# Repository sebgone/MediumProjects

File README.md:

# Electronics projects view

Medium size embedded electronics projects performed during studies.

1. [Bicycle Electronic Shifter](https://github.com/sebgone/MediumProjects/tree/main/Bicycle%20Electric%20Shifter)
2. [Blinds Control System](https://github.com/sebgone/MediumProjects/tree/main/Blinds%20Control%20System)
3. [Machine Learning Position Tracker](https://github.com/sebgone/MediumProjects/tree/main/Mchnie%20Learning%20Position%20Tracker)

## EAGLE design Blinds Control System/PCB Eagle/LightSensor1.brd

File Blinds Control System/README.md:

# Blinds Control System

The purpose of this project was designing and building a control system for monitoring and setting the amount of sunlight in the room. The major assumption was based on making use of wireless solutions to communicate between elements of control system. Its parts consist of regulator, driver element and sensors. The functioning comes to read data from light sensors compare this value with desired value and then applies the difference as a control signal to steer a roller blinds by DC motor. 

## Technology:
* Arduino 
* Ethernet Shield
* Bluetooth

## Application:
The system consist of four elements. Central Module is a master device which supervise data comunication beetwen DC controler and bluetooth sensors. 
User has accesss by a web browser to set a specific light level or read actual value. Sensors send readings to master and it calculte average. 
The calculated value is compared with desired value. Next, based on difference range DC controler get up or down blinds.    

## specificaton:
- Four elements of a system
- Bluetooth communication
- Sensor battery supply
- Controlling web page
- Limit switches 
- DC motor with metal gear
---
## Design:
* ### Source Code:
  * [source code](https://github.com/sebgone/MediumProjects/tree/sebgone-update/Blinds%20Control%20System/Source%20Code)  

* ### Block Scheme:

* ### Circuit Diagram:
&nbsp;
&nbsp;

  * Central module

&nbsp;
&nbsp;

  * Driver

&nbsp;
&nbsp;

  * Light Sensor

* ### Circuit Eagle schematic:
&nbsp;
&nbsp;

   * Light Sensor 

&nbsp;
&nbsp;

   * Motor Driver 

* ### Circuit Eagle PCB layout:
&nbsp;
&nbsp;

  * Light Sensor

&nbsp;
&nbsp;

  * Moto Driver

* ### Web Page:

* ### Assembled device:

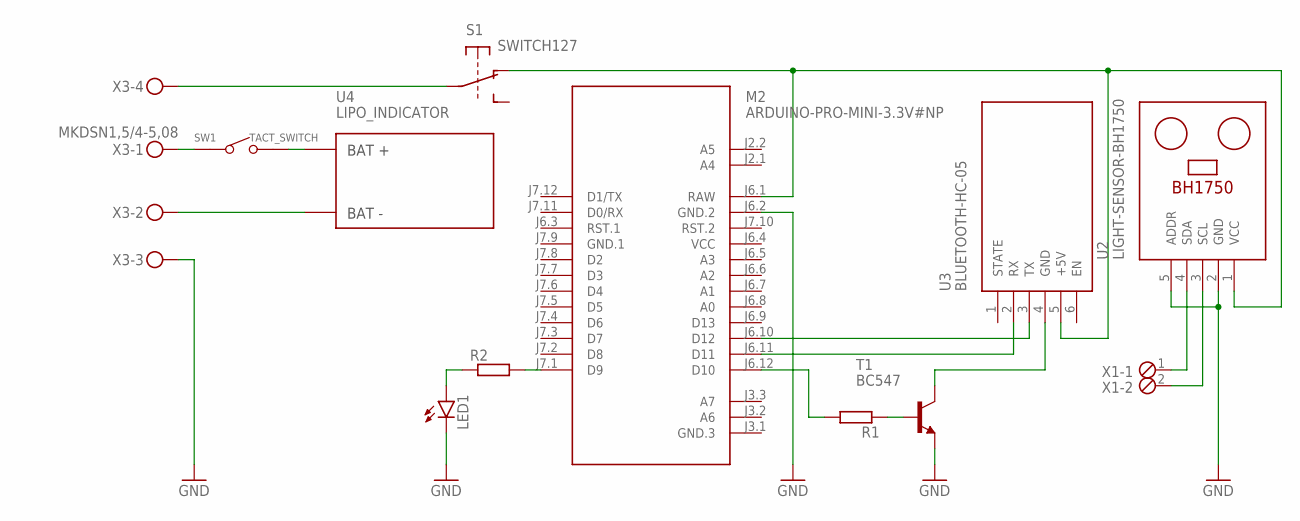
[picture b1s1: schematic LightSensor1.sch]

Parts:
LED1: LED3MM
M2: ARDUINO-PRO-MINI-3.3V#NP; ARDUINO-PRO-MINI#NP
R1, R2: R-EU_0207/10; 0207/10
S1: SWITCH127
SW1: TACT_SWITCH; SW2-5.0-6.0X3.0X4.3MM
T1: BC547; TO92
U2: LIGHT-SENSOR-BH1750
U3: BLUETOOTH-HC-05; WIRELESS-BLUETOOTH-HC-05
U4: LIPO_INDICATOR; INDICATROR_NR1
X1: MPT2; 2POL254
X3: MKDSN1,5/4-5,08

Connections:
GND: LED1.K (C), M2.J6.2 (GND.2), T1.1 (E), U2.2 (GND), U2.5 (ADDR), X3.3
GND.1: M2.J7.9 (GND.1)
unnamed: U4.-BAT, X3.2
unnamed: SW1.2, U4.+BAT
unnamed: SW1.1, X3.1
unnamed: M2.J6.11 (D11), U3.2 (RX)
unnamed: S1.P$2 (2), X3.4
unnamed: LED1.A, R2.1
unnamed: M2.J6.1 (RAW), S1.P$3 (3), U2.1 (VCC), U3.5 (+5V)
unnamed: M2.J7.1 (D9), R2.2
unnamed: M2.J6.10 (D12), U3.3 (TX)
unnamed: M2.J6.12 (D10), R1.2
unnamed: R1.1, T1.2 (B)
unnamed: T1.3 (C), U3.4 (GND)
unnamed: U2.4 (SDA), X1.1
unnamed: U2.3 (SCL), X1.2
VCC: M2.J6.4 (VCC)

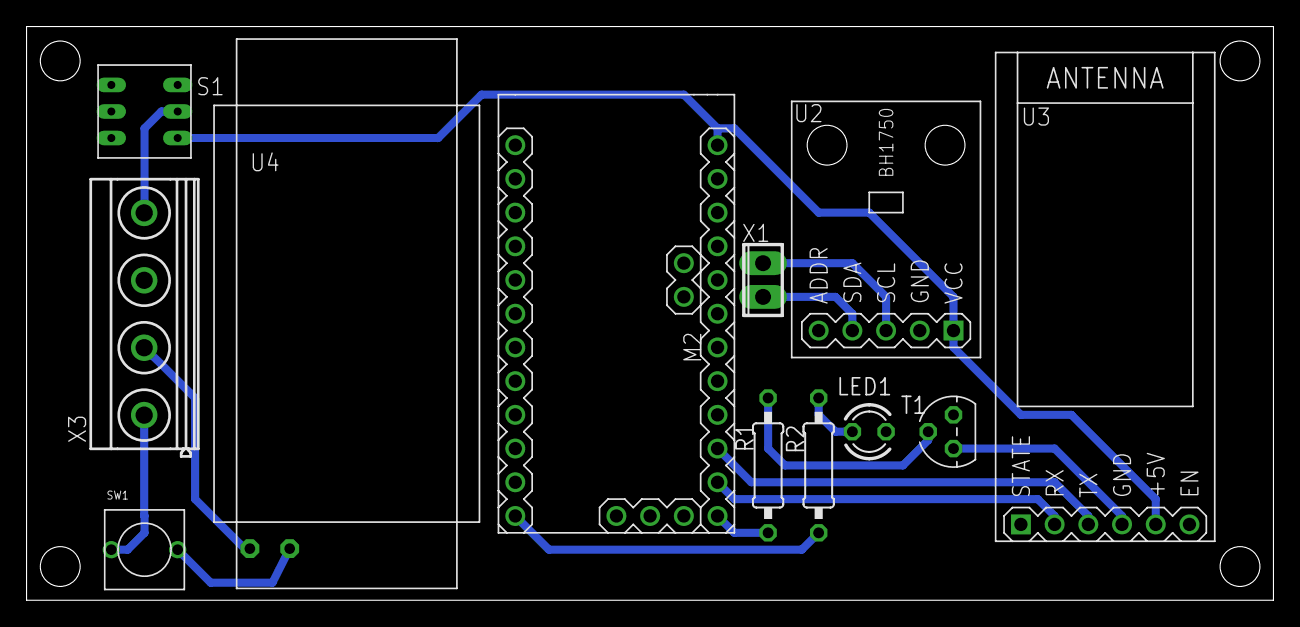
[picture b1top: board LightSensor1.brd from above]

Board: 2 copper layers, 94.0 x 43.2 mm, 12 parts (0 on the bottom side), 15 nets.

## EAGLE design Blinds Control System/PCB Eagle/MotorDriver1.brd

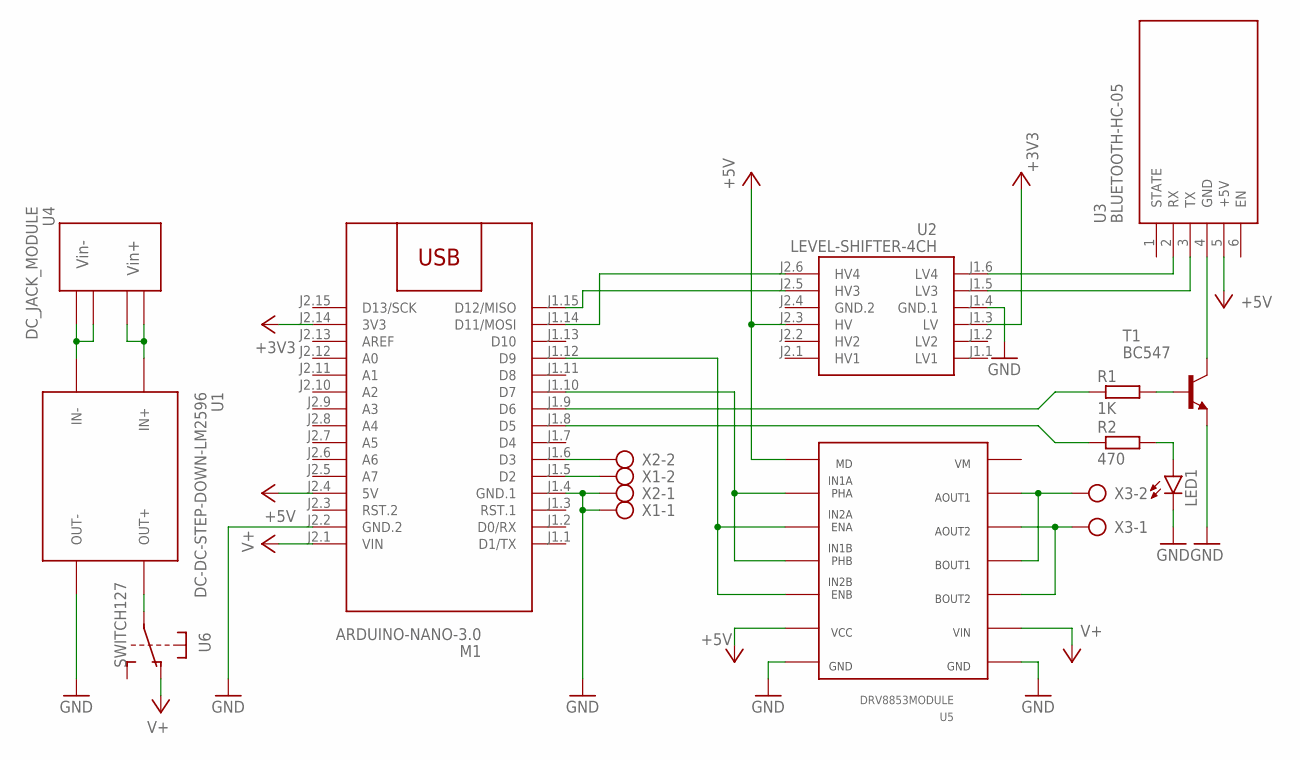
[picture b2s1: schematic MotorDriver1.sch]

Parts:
LED1: LED3MM
M1: ARDUINO-NANO-3.0
R1: 1K; 0207/7
R2: 470; 0207/7
T1: BC547; TO92
U1: DC-DC-STEP-DOWN-LM2596
U2: LEVEL-SHIFTER-4CH
U3: BLUETOOTH-HC-05; WIRELESS-BLUETOOTH-HC-05
U4: DC_JACK_MODULE; MA04-1
U5: DRV8853MODULE; DIL14
U6: SWITCH127
X1, X2, X3: AK500/2

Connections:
+3V3: M1.J2.14 (3V3), U2.J1.3 (LV)
+5V: M1.J2.4 (5V), U2.J2.3 (HV), U3.5 (+5V), U5.9, U5.14
GND: LED1.K (C), M1.J1.4 (GND.1), M1.J2.2 (GND.2), T1.1 (E), U1.OUT-, U2.J1.4 (GND.1), U5.1, U5.8, X1.1, X2.1
GND.2: U2.J2.4 (GND.2)
unnamed: U1.IN+, U4.1, U4.2
unnamed: U1.IN-, U4.3, U4.4
unnamed: M1.J1.6 (D3), X2.2
unnamed: M1.J1.10 (D7), U5.11, U5.13
unnamed: M1.J1.12 (D9), U5.10, U5.12
unnamed: U5.4, U5.6, X3.2
unnamed: M1.J1.5 (D2), X1.2
unnamed: U1.OUT+, U6.P$2 (2)
unnamed: M1.J1.8 (D5), R2.1
unnamed: M1.J1.14 (D11/MOSI), U2.J2.6 (HV4)
unnamed: M1.J1.15 (D12/MISO), U2.J2.5 (HV3)
unnamed: M1.J1.9 (D6), R1.1
unnamed: U5.3, U5.5, X3.1
unnamed: R1.2, T1.2 (B)
unnamed: T1.3 (C), U3.4 (GND)
unnamed: LED1.A, R2.2
unnamed: U2.J1.6 (LV4), U3.2 (RX)
unnamed: U2.J1.5 (LV3), U3.3 (TX)
V+: M1.J2.1 (VIN), U5.2, U6.P$3 (3)

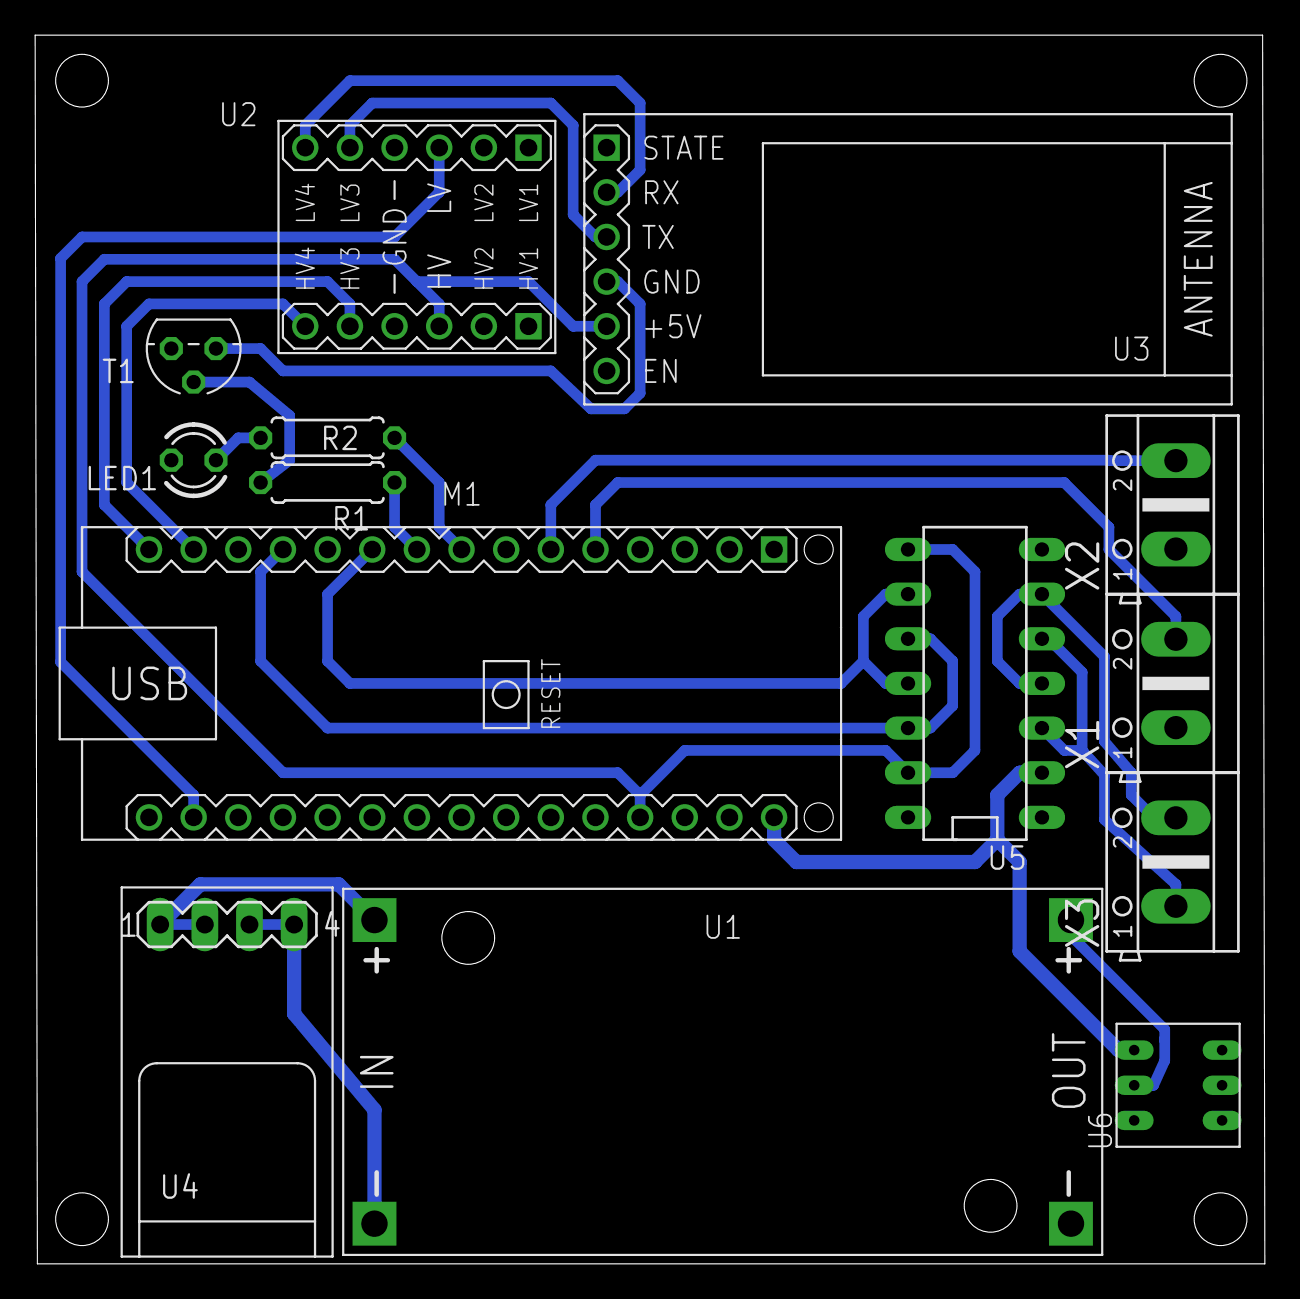
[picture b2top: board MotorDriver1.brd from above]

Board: 2 copper layers, 70.0 x 69.9 mm, 14 parts (0 on the bottom side), 22 nets.

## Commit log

2022-05-07 Readme updates
    Update readme links
2022-05-07 Readme updates (#1)
    * Readme updates
    Update readme links
    * Readme updates
    Update readme links
    * Readme updates
    Update readme links
2022-05-07 Correction
2023-05-15 Sebgone update (#2)
    * Readme updates
    Update readme links
    * Readme updates
    Update readme links
    * Readme updates
    Update readme links

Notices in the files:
parts and their libraries:
diy-modules: Released under the Creative Commons Attribution 4.0 International License: http://creativecommons.org/licenses/by/4.0
